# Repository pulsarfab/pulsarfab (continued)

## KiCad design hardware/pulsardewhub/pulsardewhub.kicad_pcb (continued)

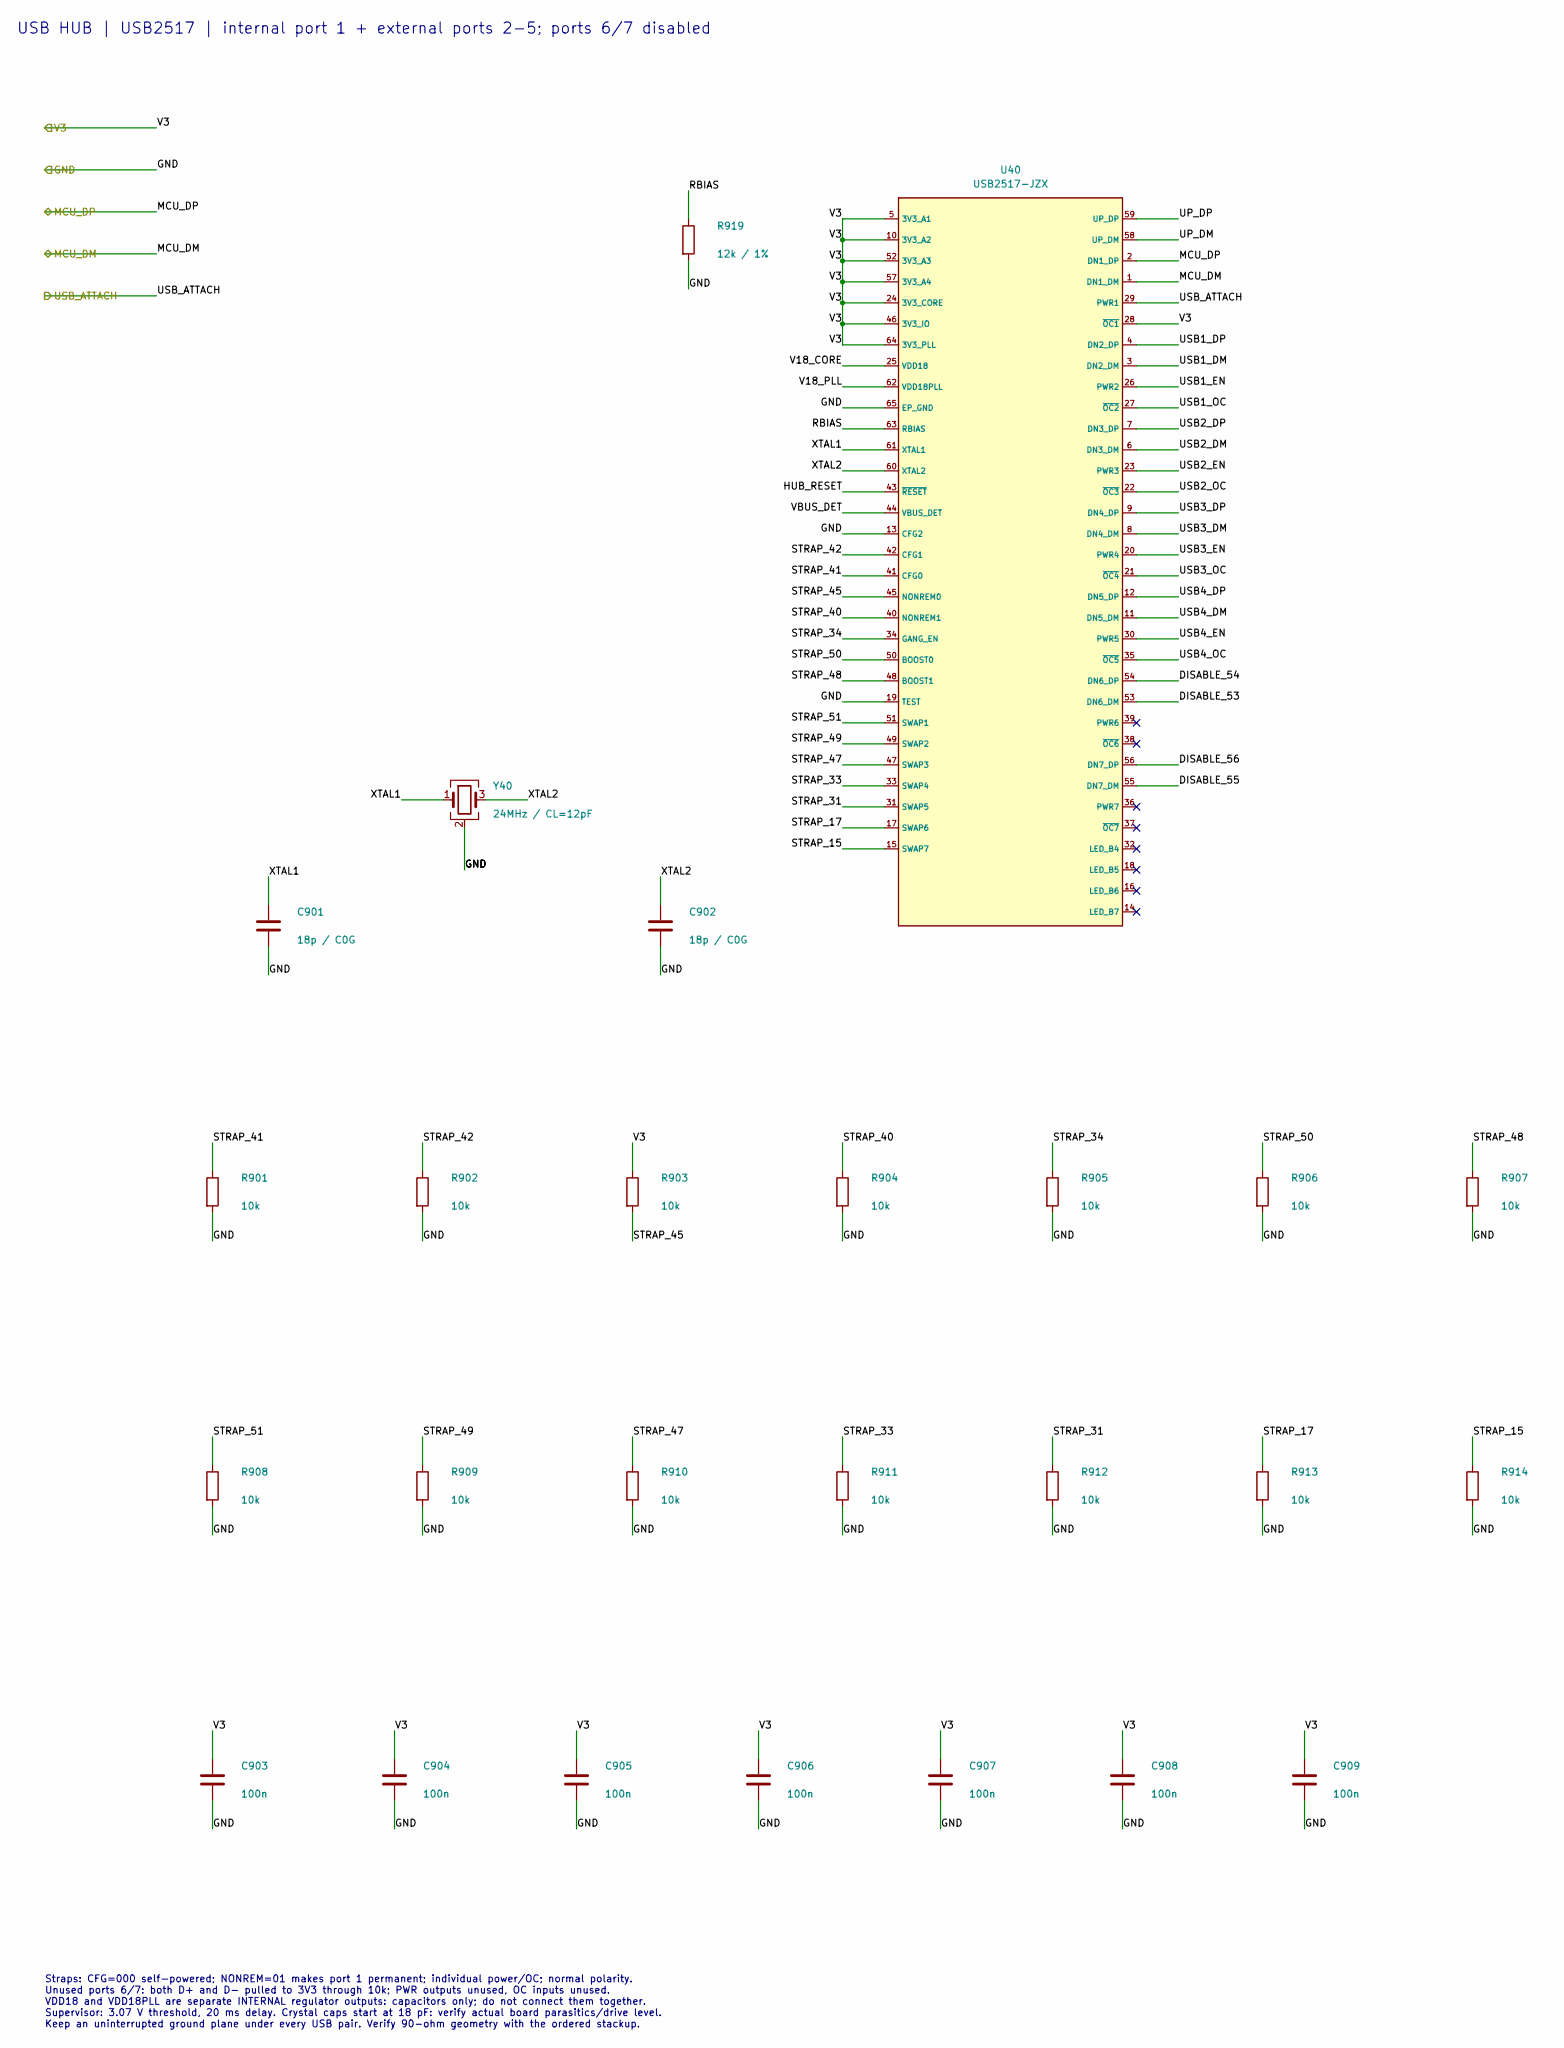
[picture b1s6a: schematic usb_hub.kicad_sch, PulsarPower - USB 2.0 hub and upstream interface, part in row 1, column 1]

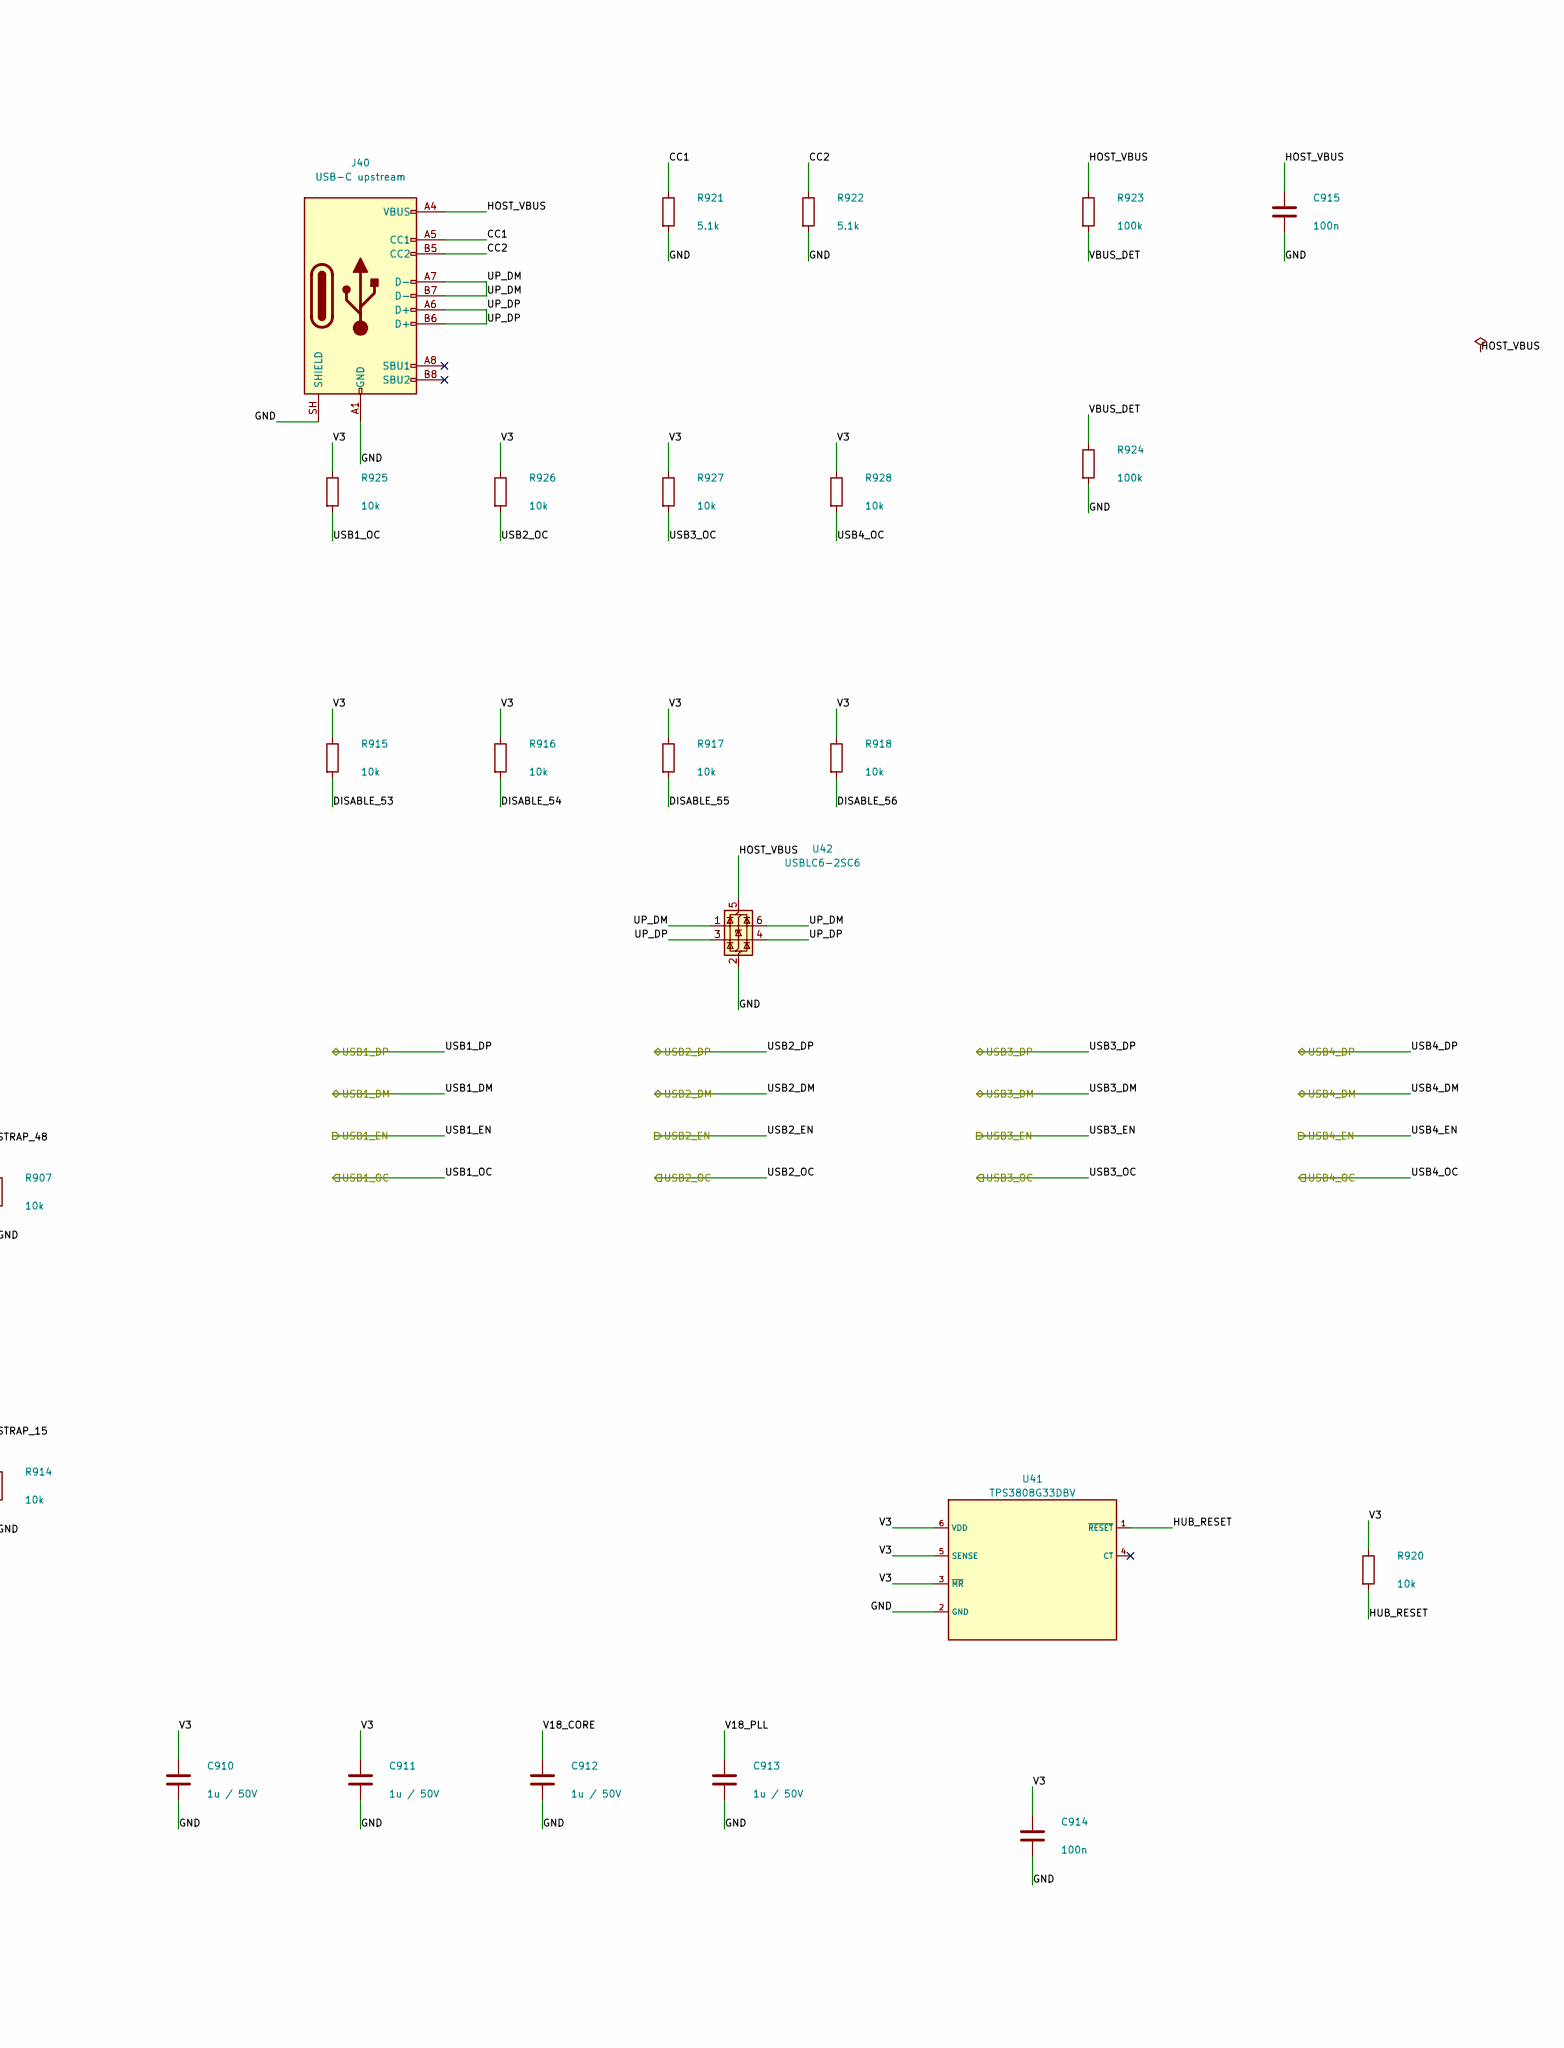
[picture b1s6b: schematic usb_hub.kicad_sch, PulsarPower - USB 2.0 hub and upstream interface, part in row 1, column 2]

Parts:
C901, C902: 18p / C0G; C_0603_1608Metric; MPN CGA3E2C0G1H180JT0Y0N; LCSC C342890
C903, C904, C905, C906, C907, C908, C909, C914, C915: 100n; C_0603_1608Metric; MPN CC0603KRX7R9BB104; LCSC C14663
C910, C911, C912, C913: 1u / 50V; C_0603_1608Metric; MPN CL10A105KB8NNNC; LCSC C15849
J40: USB-C upstream; USB_C_HRO_TYPE-C-31-M-12; MPN TYPE-C-31-M-12; LCSC C165948
R901, R902, R903, R904, R905, R906, R907, R908, R909, R910, R911, R912, R913, R914, R915, R916, R917, R918, R920, R925, R926, R927, R928: 10k; R_0603_1608Metric; MPN 0603WAF1002T5E; LCSC C25804
R919: 12k / 1%; R_0603_1608Metric; MPN 0603WAF1202T5E; LCSC C22790
R921, R922: 5.1k; R_0603_1608Metric; MPN 0603WAF5101T5E; LCSC C23186
R923, R924: 100k; R_0603_1608Metric; MPN 0603WAF1003T5E; LCSC C25803
U40: USB2517-JZX; QFN-64-1EP_9x9mm_P0.5mm_EP4.7x4.7mm; MPN USB2517-JZX; LCSC C1521556
U41: TPS3808G33DBV; SOT-23-6; MPN TPS3808G33DBVR; LCSC C43698
U42: USBLC6-2SC6; SOT-23-6; MPN USBLC6-2SC6; LCSC C7519
Y40: 24MHz / CL=12pF; Crystal_SMD_3225-4Pin_3.2x2.5mm; MPN 3225 24M 12PF 10PPM; LCSC C5181479

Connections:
/GND: C901.2, C902.2, C903.2, C904.2, C905.2, C906.2, C907.2, C908.2, C909.2, C910.2, C911.2, C912.2, C913.2, C914.2, C915.2, J40.A1 (GND), J40.A12 (GND), J40.B1 (GND), J40.B12 (GND), J40.SH (SHIELD), R901.2, R902.2, R904.2, R905.2, R906.2, R907.2, R908.2, R909.2, R910.2, R911.2, R912.2, R913.2, R914.2, R919.2, R921.2, R922.2, R924.2, U40.13 (CFG2), U40.19 (TEST), U40.65 (EP_GND), U41.2 (GND), U42.2 (GND), Y40.2 (G), Y40.4 (G); also elsewhere on the board
/MCU_DM: U40.1 (DN1_DM); also elsewhere on the board
/MCU_DP: U40.2 (DN1_DP); also elsewhere on the board
/USB1_DM: U40.3 (DN2_DM); also elsewhere on the board
/USB1_DP: U40.4 (DN2_DP); also elsewhere on the board
/USB1_EN: U40.26 (PWR2); also elsewhere on the board
/USB1_OC: R925.2, U40.27 (~OC2); also elsewhere on the board
/USB2_DM: U40.6 (DN3_DM); also elsewhere on the board
/USB2_DP: U40.7 (DN3_DP); also elsewhere on the board
/USB2_EN: U40.23 (PWR3); also elsewhere on the board
/USB2_OC: R926.2, U40.22 (~OC3); also elsewhere on the board
/USB3_DM: U40.8 (DN4_DM); also elsewhere on the board
/USB3_DP: U40.9 (DN4_DP); also elsewhere on the board
/USB3_EN: U40.20 (PWR4); also elsewhere on the board
/USB3_OC: R927.2, U40.21 (~OC4); also elsewhere on the board
/USB4_DM: U40.11 (DN5_DM); also elsewhere on the board
/USB4_DP: U40.12 (DN5_DP); also elsewhere on the board
/USB4_EN: U40.30 (PWR5); also elsewhere on the board
/USB4_OC: R928.2, U40.35 (~OC5); also elsewhere on the board
/USB hub/CC1: J40.A5 (CC1), R921.1
/USB hub/CC2: J40.B5 (CC2), R922.1
/USB hub/DISABLE_53: R915.2, U40.53 (DN6_DM)
/USB hub/DISABLE_54: R916.2, U40.54 (DN6_DP)
/USB hub/DISABLE_55: R917.2, U40.55 (DN7_DM)
/USB hub/DISABLE_56: R918.2, U40.56 (DN7_DP)
/USB hub/HOST_VBUS: C915.1, J40.A4 (VBUS), J40.A9 (VBUS), J40.B4 (VBUS), J40.B9 (VBUS), R923.1, U42.5 (VBUS)
/USB hub/HUB_RESET: R920.2, U40.43 (~RESET), U41.1 (~RESET)
/USB hub/RBIAS: R919.1, U40.63 (RBIAS)
/USB hub/STRAP_15: R914.1, U40.15 (SWAP7)
/USB hub/STRAP_17: R913.1, U40.17 (SWAP6)
/USB hub/STRAP_31: R912.1, U40.31 (SWAP5)
/USB hub/STRAP_33: R911.1, U40.33 (SWAP4)
/USB hub/STRAP_34: R905.1, U40.34 (GANG_EN)
/USB hub/STRAP_40: R904.1, U40.40 (NONREM1)
/USB hub/STRAP_41: R901.1, U40.41 (CFG0)
/USB hub/STRAP_42: R902.1, U40.42 (CFG1)
/USB hub/STRAP_45: R903.2, U40.45 (NONREM0)
/USB hub/STRAP_47: R910.1, U40.47 (SWAP3)
/USB hub/STRAP_48: R907.1, U40.48 (BOOST1)
/USB hub/STRAP_49: R909.1, U40.49 (SWAP2)
/USB hub/STRAP_50: R906.1, U40.50 (BOOST0)
/USB hub/STRAP_51: R908.1, U40.51 (SWAP1)
/USB hub/UP_DM: J40.A7 (D-), J40.B7 (D-), U40.58 (UP_DM), U42.1 (I/O1), U42.6 (I/O1)
/USB hub/UP_DP: J40.A6 (D+), J40.B6 (D+), U40.59 (UP_DP), U42.3 (I/O2), U42.4 (I/O2)
/USB hub/V18_CORE: C912.1, U40.25 (VDD18)
/USB hub/V18_PLL: C913.1, U40.62 (VDD18PLL)
/USB hub/VBUS_DET: R923.2, R924.1, U40.44 (VBUS_DET)
/USB hub/XTAL1: C901.1, U40.61 (XTAL1), Y40.1
/USB hub/XTAL2: C902.1, U40.60 (XTAL2), Y40.3
/USB_ATTACH: U40.29 (PWR1); also elsewhere on the board
/V3: C903.1, C904.1, C905.1, C906.1, C907.1, C908.1, C909.1, C910.1, C911.1, C914.1, R903.1, R915.1, R916.1, R917.1, R918.1, R920.1, R925.1, R926.1, R927.1, R928.1, U40.5 (3V3_A1), U40.10 (3V3_A2), U40.24 (3V3_CORE), U40.28 (~OC1), U40.46 (3V3_IO), U40.52 (3V3_A3), U40.57 (3V3_A4), U40.64 (3V3_PLL), U41.3 (~MR), U41.5 (SENSE), U41.6 (VDD); also elsewhere on the board

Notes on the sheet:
USB HUB | USB2517 | internal port 1 + external ports 2-5; ports 6/7 disabled
Straps: CFG=000 self-powered; NONREM=01 makes port 1 permanent; individual power/OC; normal polarity. Unused ports 6/7: both D+ and D- pulled to 3V3 through 10k; PWR outputs unused, OC inputs unused. VDD18 and VDD18PLL are separate INTERNAL regulator outputs: capacitors only; do not connect them to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

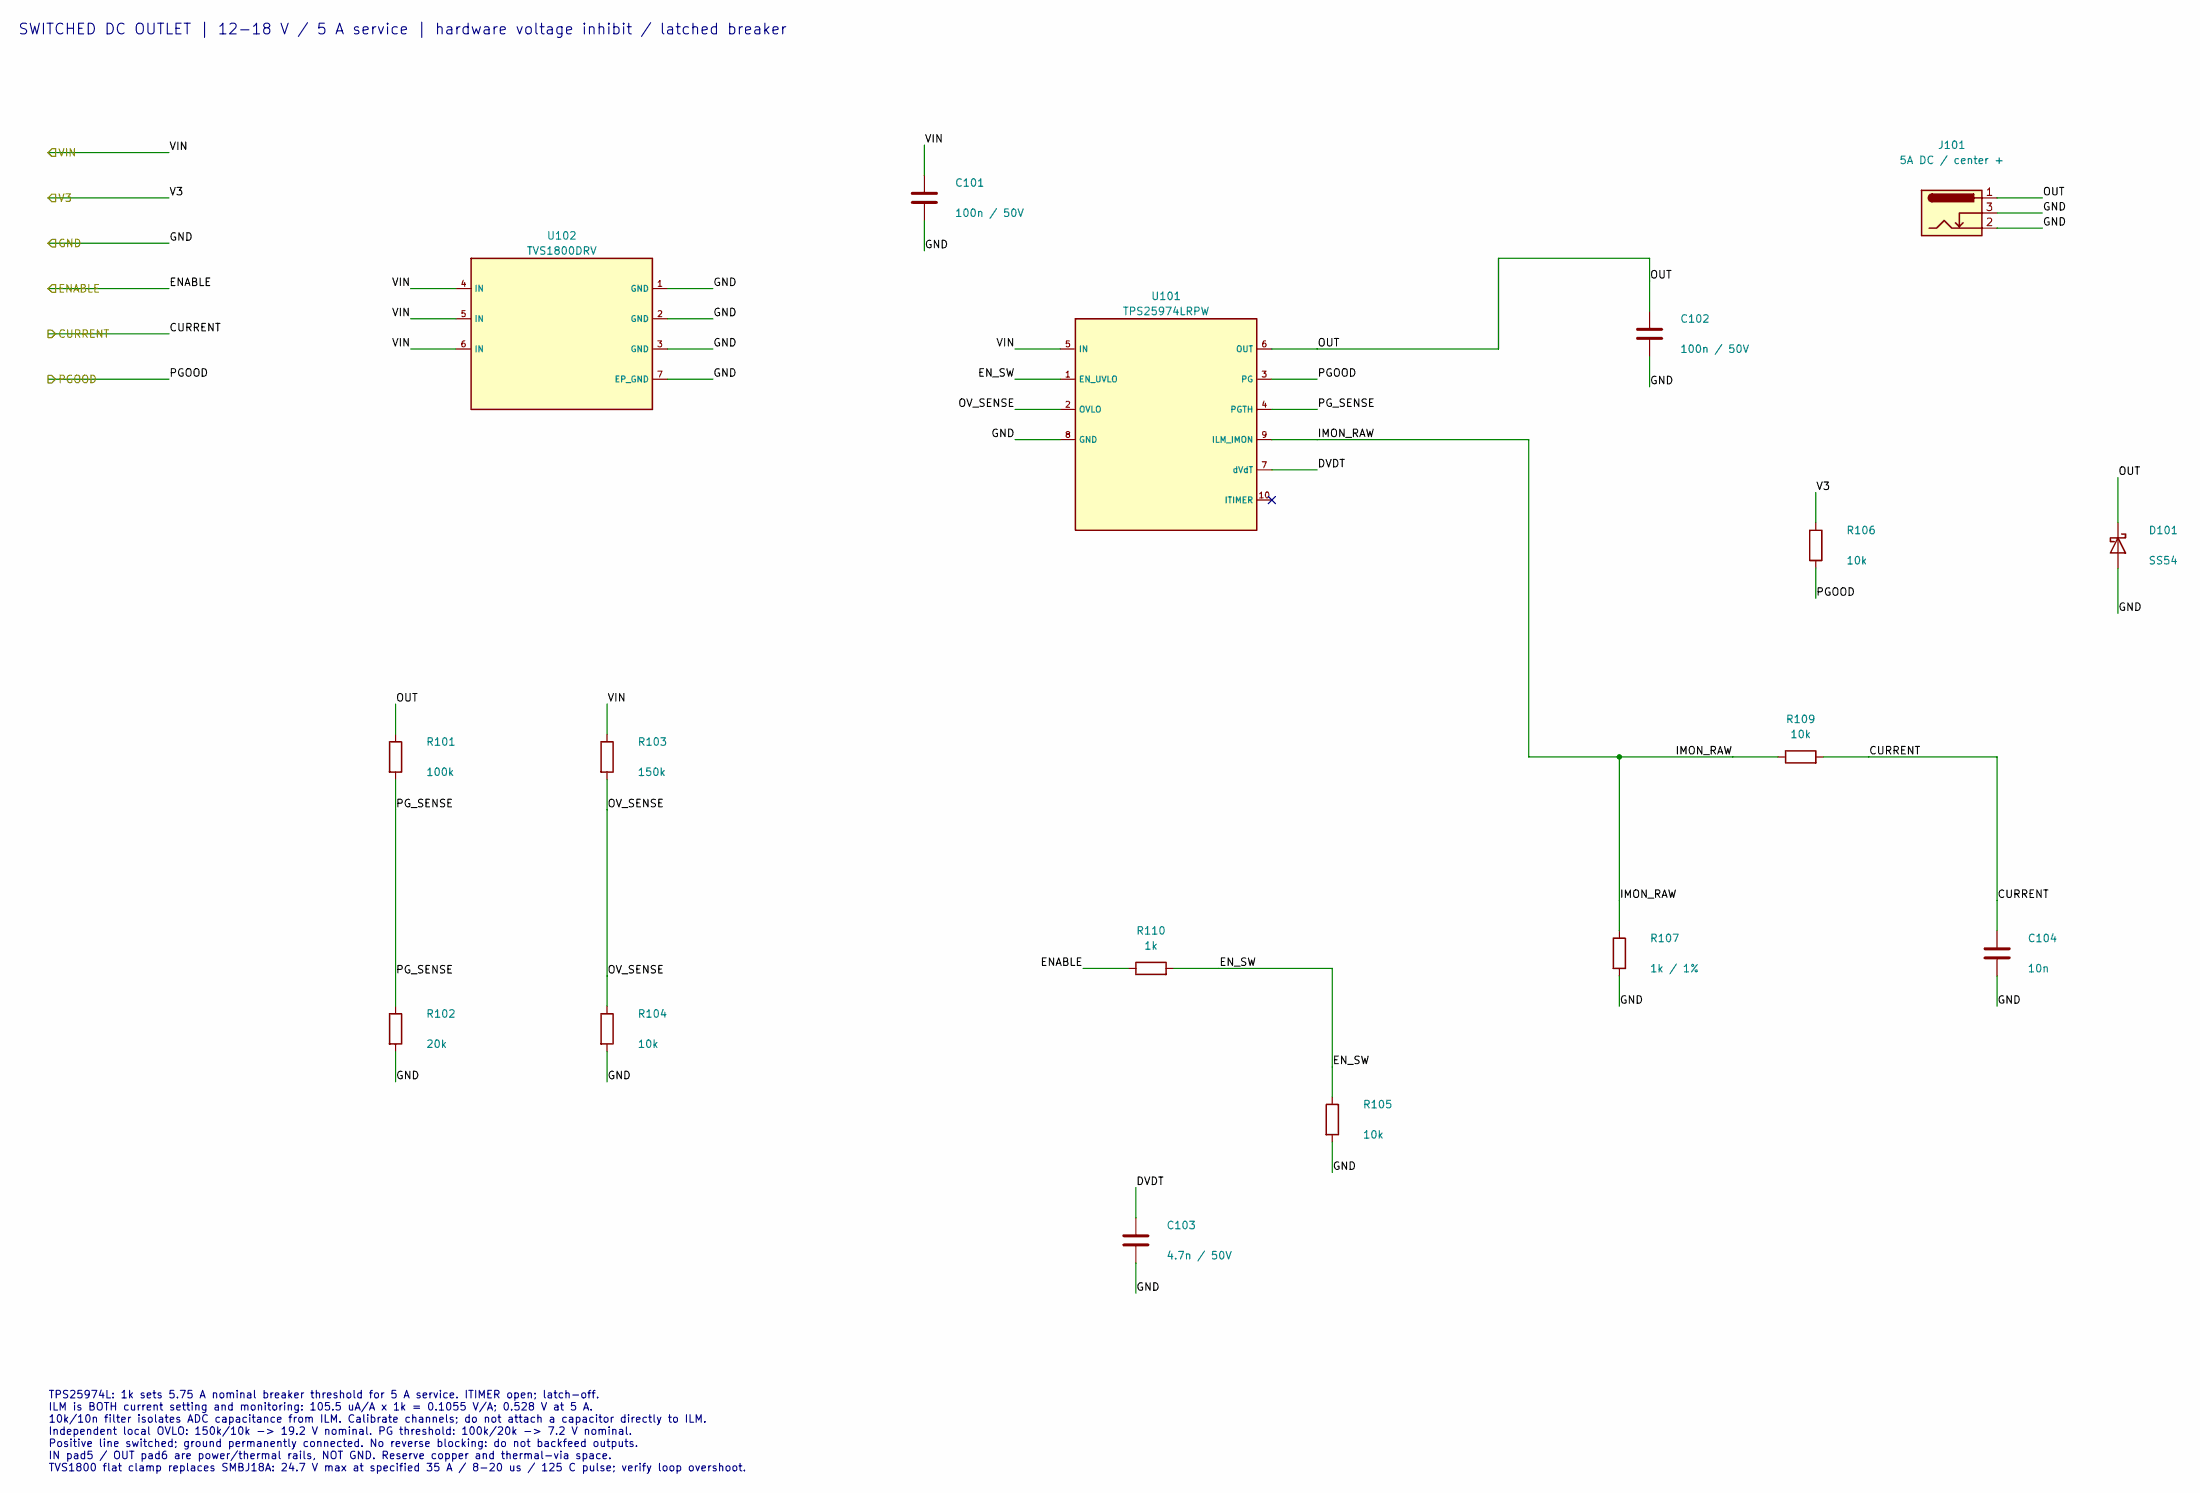
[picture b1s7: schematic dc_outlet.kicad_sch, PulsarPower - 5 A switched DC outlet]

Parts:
C101, C102: 100n / 50V; C_0603_1608Metric; MPN CC0603KRX7R9BB104; LCSC C14663
C103: 4.7n / 50V; C_0603_1608Metric; MPN CL10B472KB8NNNC; LCSC C1621
C104: 10n; C_0603_1608Metric; MPN CL10B103KB8NNNC; LCSC C1589
D101: SS54; D_SMA; MPN SS54; LCSC C22452
J101: 5A DC / center +; BarrelJack_XKB_DC-005K-5A_Edge; MPN DC-005K-5A-2.0; LCSC C2880546
R101: 100k; R_0603_1608Metric; MPN 0603WAF1003T5E; LCSC C25803
R102: 20k; R_0603_1608Metric; MPN 0603WAF2002T5E; LCSC C4184
R103: 150k; R_0603_1608Metric; MPN 0603WAF1503T5E; LCSC C22807
R104, R105, R106, R109: 10k; R_0603_1608Metric; MPN 0603WAF1002T5E; LCSC C25804
R107: 1k / 1%; R_0603_1608Metric; MPN 0603WAF1001T5E; LCSC C21190
R110: 1k; R_0603_1608Metric; MPN 0603WAF1001T5E; LCSC C21190
U101: TPS25974LRPW; TI_RPW0010A_VQFN10_2x2mm; MPN TPS25974LRPWR; LCSC C3662931
U102: TVS1800DRV; WSON-6-1EP_2x2mm_P0.65mm_EP1x1.6mm; MPN TVS1800DRVR; LCSC C2649846

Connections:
/DC outlet 1/DVDT: C103.1, U101.7 (dVdT)
/DC outlet 1/EN_SW: R105.1, R110.2, U101.1 (EN_UVLO)
/DC outlet 1/IMON_RAW: R107.1, R109.1, U101.9 (ILM_IMON)
/DC outlet 1/OUT: C102.1, D101.1 (K), J101.1, R101.1, U101.6 (OUT)
/DC outlet 1/OV_SENSE: R103.2, R104.1, U101.2 (OVLO)
/DC outlet 1/PG_SENSE: R101.2, R102.1, U101.4 (PGTH)
/DC_PG1: R106.2, U101.3 (PG); also elsewhere on the board
/DC_SAFE1: R110.1; also elsewhere on the board
/GND: C101.2, C102.2, C103.2, C104.2, D101.2 (A), J101.2, J101.3, R102.2, R104.2, R105.2, R107.2, U101.8 (GND), U102.1 (GND), U102.2 (GND), U102.3 (GND), U102.7 (EP_GND); also elsewhere on the board
/IMON1: C104.1, R109.2; also elsewhere on the board
/V3: R106.1; also elsewhere on the board
/VIN: C101.1, R103.1, U101.5 (IN), U102.4 (IN), U102.5 (IN), U102.6 (IN); also elsewhere on the board

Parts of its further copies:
C201, C202, C301, C302, C401, C402: 100n / 50V; C_0603_1608Metric; MPN CC0603KRX7R9BB104; LCSC C14663
C203, C303, C403: 4.7n / 50V; C_0603_1608Metric; MPN CL10B472KB8NNNC; LCSC C1621
C204, C304, C404: 10n; C_0603_1608Metric; MPN CL10B103KB8NNNC; LCSC C1589
D201, D301, D401: SS54; D_SMA; MPN SS54; LCSC C22452
J201, J301, J401: 5A DC / center +; BarrelJack_XKB_DC-005K-5A_Edge; MPN DC-005K-5A-2.0; LCSC C2880546
R201, R301, R401: 100k; R_0603_1608Metric; MPN 0603WAF1003T5E; LCSC C25803
R202, R302, R402: 20k; R_0603_1608Metric; MPN 0603WAF2002T5E; LCSC C4184
R203, R303, R403: 150k; R_0603_1608Metric; MPN 0603WAF1503T5E; LCSC C22807
R204, R205, R206, R209, R304, R305, R306, R309, R404, R405, R406, R409: 10k; R_0603_1608Metric; MPN 0603WAF1002T5E; LCSC C25804
R207, R307, R407: 1k / 1%; R_0603_1608Metric; MPN 0603WAF1001T5E; LCSC C21190
R210, R310, R410: 1k; R_0603_1608Metric; MPN 0603WAF1001T5E; LCSC C21190
U201, U301, U401: TPS25974LRPW; TI_RPW0010A_VQFN10_2x2mm; MPN TPS25974LRPWR; LCSC C3662931
U202, U302, U402: TVS1800DRV; WSON-6-1EP_2x2mm_P0.65mm_EP1x1.6mm; MPN TVS1800DRVR; LCSC C2649846

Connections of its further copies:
/DC outlet 2/DVDT: C203.1, U201.7 (dVdT)
/DC outlet 2/EN_SW: R205.1, R210.2, U201.1 (EN_UVLO)
/DC outlet 2/IMON_RAW: R207.1, R209.1, U201.9 (ILM_IMON)
/DC outlet 2/OUT: C202.1, D201.1 (K), J201.1, R201.1, U201.6 (OUT)
/DC outlet 2/OV_SENSE: R203.2, R204.1, U201.2 (OVLO)
/DC outlet 2/PG_SENSE: R201.2, R202.1, U201.4 (PGTH)
/DC outlet 3/DVDT: C303.1, U301.7 (dVdT)
/DC outlet 3/EN_SW: R305.1, R310.2, U301.1 (EN_UVLO)
/DC outlet 3/IMON_RAW: R307.1, R309.1, U301.9 (ILM_IMON)
/DC outlet 3/OUT: C302.1, D301.1 (K), J301.1, R301.1, U301.6 (OUT)
/DC outlet 3/OV_SENSE: R303.2, R304.1, U301.2 (OVLO)
/DC outlet 3/PG_SENSE: R301.2, R302.1, U301.4 (PGTH)
/DC outlet 4/DVDT: C403.1, U401.7 (dVdT)
/DC outlet 4/EN_SW: R405.1, R410.2, U401.1 (EN_UVLO)
/DC outlet 4/IMON_RAW: R407.1, R409.1, U401.9 (ILM_IMON)
/DC outlet 4/OUT: C402.1, D401.1 (K), J401.1, R401.1, U401.6 (OUT)
/DC outlet 4/OV_SENSE: R403.2, R404.1, U401.2 (OVLO)
/DC outlet 4/PG_SENSE: R401.2, R402.1, U401.4 (PGTH)
/DC_PG2: R206.2, U201.3 (PG); also elsewhere on the board
/DC_PG3: R306.2, U301.3 (PG); also elsewhere on the board
/DC_PG4: R406.2, U401.3 (PG); also elsewhere on the board
/DC_SAFE2: R210.1; also elsewhere on the board
/DC_SAFE3: R310.1; also elsewhere on the board
/DC_SAFE4: R410.1; also elsewhere on the board
/GND: C201.2, C202.2, C203.2, C204.2, C301.2, C302.2, C303.2, C304.2, C401.2, C402.2, C403.2, C404.2, D201.2 (A), D301.2 (A), D401.2 (A), J201.2, J201.3, J301.2, J301.3, J401.2, J401.3, R202.2, R204.2, R205.2, R207.2, R302.2, R304.2, R305.2, R307.2, R402.2, R404.2, R405.2, R407.2, U201.8 (GND), U202.1 (GND), U202.2 (GND), U202.3 (GND), U202.7 (EP_GND), U301.8 (GND), U302.1 (GND), U302.2 (GND), U302.3 (GND), U302.7 (EP_GND), U401.8 (GND), U402.1 (GND), U402.2 (GND), U402.3 (GND), U402.7 (EP_GND); also elsewhere on the board
/IMON2: C204.1, R209.2; also elsewhere on the board
/IMON3: C304.1, R309.2; also elsewhere on the board
/IMON4: C404.1, R409.2; also elsewhere on the board
/V3: R206.1, R306.1, R406.1; also elsewhere on the board
/VIN: C201.1, C301.1, C401.1, R203.1, R303.1, R403.1, U201.5 (IN), U202.4 (IN), U202.5 (IN), U202.6 (IN), U301.5 (IN), U302.4 (IN), U302.5 (IN), U302.6 (IN), U401.5 (IN), U402.4 (IN), U402.5 (IN), U402.6 (IN); also elsewhere on the board

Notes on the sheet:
SWITCHED DC OUTLET | 12-18 V / 5 A service | hardware voltage inhibit / latched breaker
TPS25974L: 1k sets 5.75 A nominal breaker threshold for 5 A service. ITIMER open; latch-off. ILM is BOTH current setting and monitoring: 105.5 uA/A x 1k = 0.1055 V/A; 0.528 V at 5 A. 10k/10n filter isolates ADC capacitance from ILM. Calibrate channels; do not attach a capacitor directly to ILM. Ind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

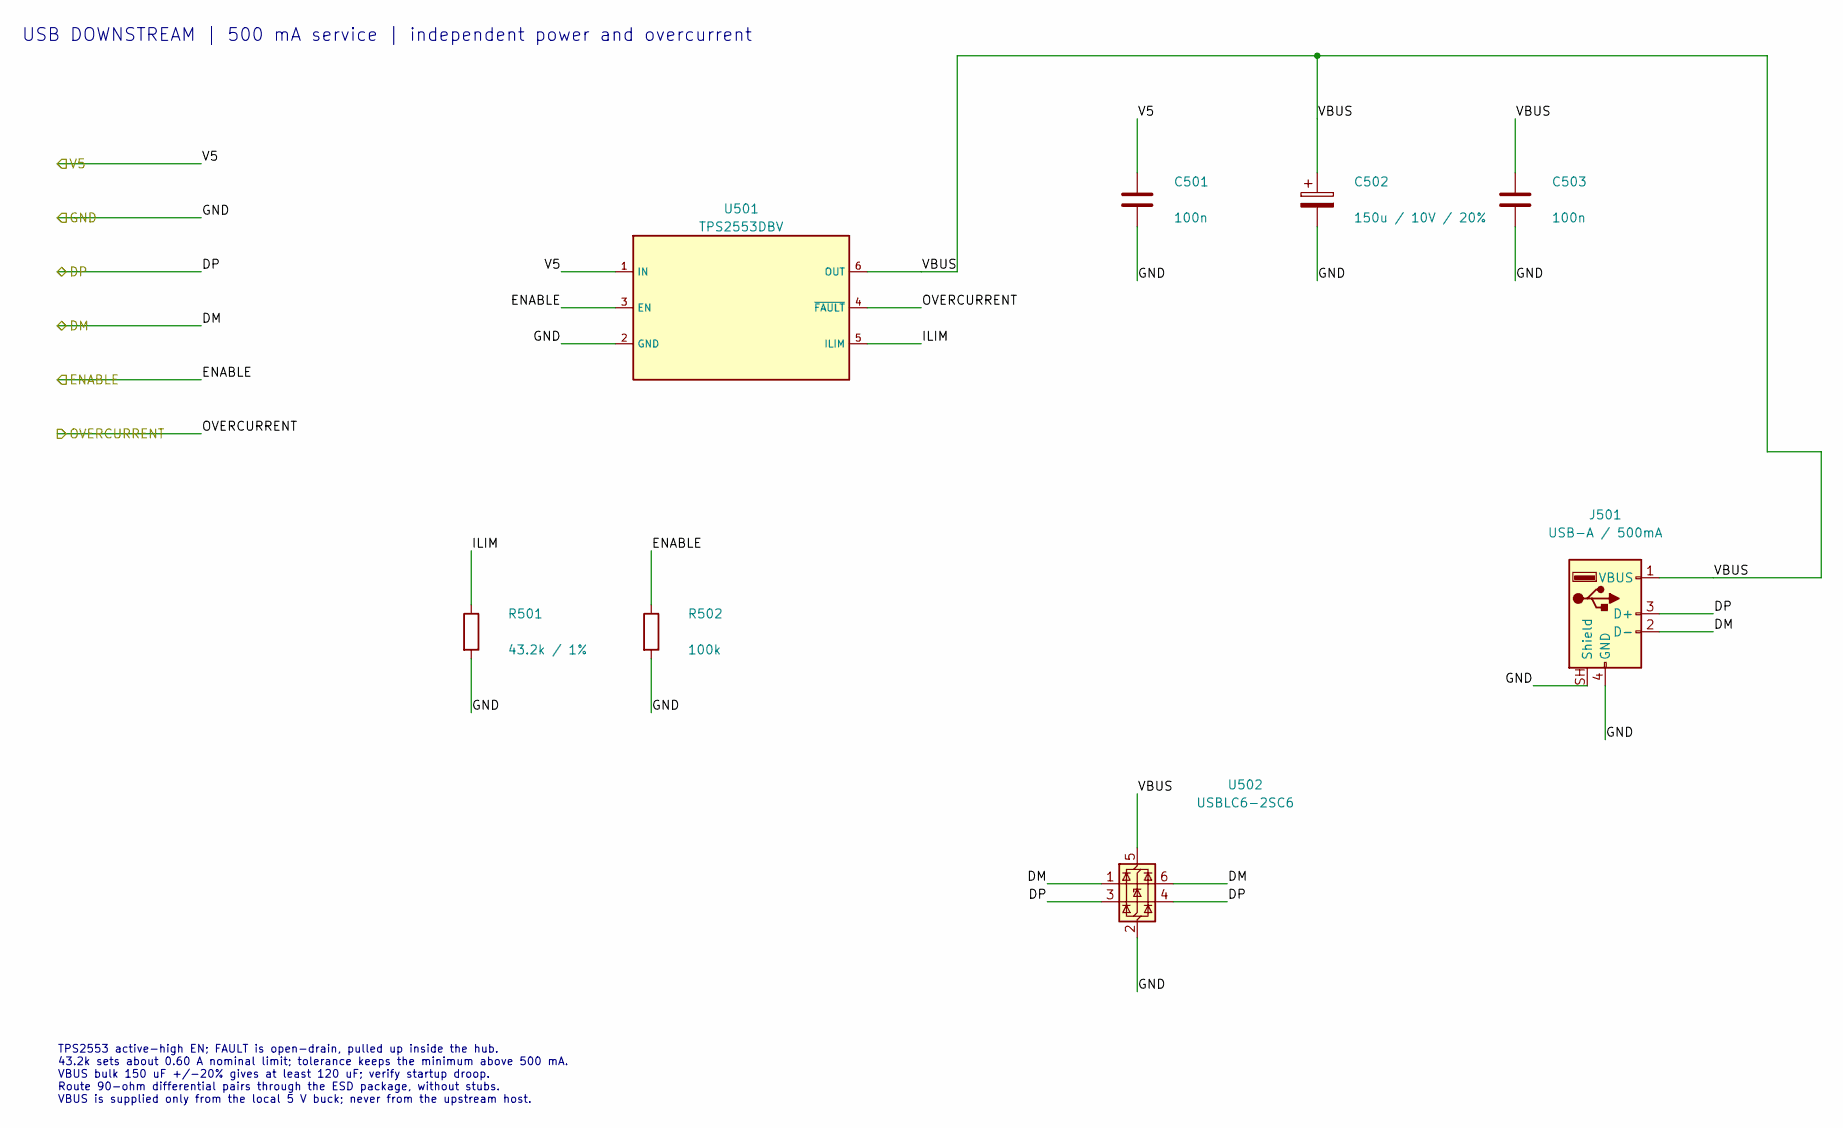
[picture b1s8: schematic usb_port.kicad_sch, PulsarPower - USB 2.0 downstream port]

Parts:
C501, C503: 100n; C_0603_1608Metric; MPN CC0603KRX7R9BB104; LCSC C14663
C502: 150u / 10V / 20%; CP_RVT_D6.3mm_L5.4mm; MPN RVT1A151M0605 150UF 10V; LCSC C970688
J501: USB-A / 500mA; USB_A_SHOUHAN_AF90ZJWG_THT; MPN AF 90 ZJWG; LCSC C456019
R501: 43.2k / 1%; R_0603_1608Metric; MPN 0603WAF4322T5E; LCSC C23053
R502: 100k; R_0603_1608Metric; MPN 0603WAF1003T5E; LCSC C25803
U501: TPS2553DBV; SOT-23-6; MPN TPS2553DBVR; LCSC C55266
U502: USBLC6-2SC6; SOT-23-6; MPN USBLC6-2SC6; LCSC C7519

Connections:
/GND: C501.2, C502.2, C503.2, J501.4 (GND), J501.SH (Shield), R501.2, R502.2, U501.2 (GND), U502.2 (GND); also elsewhere on the board
/USB1_DM: J501.2 (D-), U502.1 (I/O1), U502.6 (I/O1); also elsewhere on the board
/USB1_DP: J501.3 (D+), U502.3 (I/O2), U502.4 (I/O2); also elsewhere on the board
/USB1_EN: R502.1, U501.3 (EN); also elsewhere on the board
/USB1_OC: U501.4 (~FAULT); also elsewhere on the board
/USB port 1/ILIM: R501.1, U501.5 (ILIM)
/USB port 1/VBUS: C502.1, C503.1, J501.1 (VBUS), U501.6 (OUT), U502.5 (VBUS)
/V5: C501.1, U501.1 (IN); also elsewhere on the board

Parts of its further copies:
C601, C603, C701, C703, C801, C803: 100n; C_0603_1608Metric; MPN CC0603KRX7R9BB104; LCSC C14663
C602, C702, C802: 150u / 10V / 20%; CP_RVT_D6.3mm_L5.4mm; MPN RVT1A151M0605 150UF 10V; LCSC C970688
J601, J701, J801: USB-A / 500mA; USB_A_SHOUHAN_AF90ZJWG_THT; MPN AF 90 ZJWG; LCSC C456019
R601, R701, R801: 43.2k / 1%; R_0603_1608Metric; MPN 0603WAF4322T5E; LCSC C23053
R602, R702, R802: 100k; R_0603_1608Metric; MPN 0603WAF1003T5E; LCSC C25803
U601, U701, U801: TPS2553DBV; SOT-23-6; MPN TPS2553DBVR; LCSC C55266
U602, U702, U802: USBLC6-2SC6; SOT-23-6; MPN USBLC6-2SC6; LCSC C7519

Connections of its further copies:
/GND: C601.2, C602.2, C603.2, C701.2, C702.2, C703.2, C801.2, C802.2, C803.2, J601.4 (GND), J601.SH (Shield), J701.4 (GND), J701.SH (Shield), J801.4 (GND), J801.SH (Shield), R601.2, R602.2, R701.2, R702.2, R801.2, R802.2, U601.2 (GND), U602.2 (GND), U701.2 (GND), U702.2 (GND), U801.2 (GND), U802.2 (GND); also elsewhere on the board
/USB2_DM: J601.2 (D-), U602.1 (I/O1), U602.6 (I/O1); also elsewhere on the board
/USB2_DP: J601.3 (D+), U602.3 (I/O2), U602.4 (I/O2); also elsewhere on the board
/USB2_EN: R602.1, U601.3 (EN); also elsewhere on the board
/USB2_OC: U601.4 (~FAULT); also elsewhere on the board
/USB3_DM: J701.2 (D-), U702.1 (I/O1), U702.6 (I/O1); also elsewhere on the board
/USB3_DP: J701.3 (D+), U702.3 (I/O2), U702.4 (I/O2); also elsewhere on the board
/USB3_EN: R702.1, U701.3 (EN); also elsewhere on the board
/USB3_OC: U701.4 (~FAULT); also elsewhere on the board
/USB4_DM: J801.2 (D-), U802.1 (I/O1), U802.6 (I/O1); also elsewhere on the board
/USB4_DP: J801.3 (D+), U802.3 (I/O2), U802.4 (I/O2); also elsewhere on the board
/USB4_EN: R802.1, U801.3 (EN); also elsewhere on the board
/USB4_OC: U801.4 (~FAULT); also elsewhere on the board
/USB port 2/ILIM: R601.1, U601.5 (ILIM)
/USB port 2/VBUS: C602.1, C603.1, J601.1 (VBUS), U601.6 (OUT), U602.5 (VBUS)
/USB port 3/ILIM: R701.1, U701.5 (ILIM)
/USB port 3/VBUS: C702.1, C703.1, J701.1 (VBUS), U701.6 (OUT), U702.5 (VBUS)
/USB port 4/ILIM: R801.1, U801.5 (ILIM)
/USB port 4/VBUS: C802.1, C803.1, J801.1 (VBUS), U801.6 (OUT), U802.5 (VBUS)
/V5: C601.1, C701.1, C801.1, U601.1 (IN), U701.1 (IN), U801.1 (IN); also elsewhere on the board

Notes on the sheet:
USB DOWNSTREAM | 500 mA service | independent power and overcurrent
TPS2553 active-high EN; FAULT is open-drain, pulled up inside the hub. 43.2k sets about 0.60 A nominal limit; tolerance keeps the minimum above 500 mA. VBUS bulk 150 uF +/-20% gives at least 120 uF; verify startup droop. Route 90-ohm differential pairs through the ESD package, without stubs. VBUS i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

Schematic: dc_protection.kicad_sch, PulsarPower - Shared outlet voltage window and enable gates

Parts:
C70, C71: 100n; C_0603_1608Metric; MPN CC0603KRX7R9BB104; LCSC C14663
R70: 220k; R_0603_1608Metric; MPN 0603WAF2203T5E; LCSC C22961
R71, R73, R74, R75, R76, R77, R78: 10k; R_0603_1608Metric; MPN 0603WAF1002T5E; LCSC C25804
R72: 470k; R_0603_1608Metric; MPN 0603WAF4703T5E; LCSC C23178
U70: TPS3700DDC; SOT-23-6; MPN TPS3700DDCR; LCSC C33002
U71: SN74LVC08APW; TSSOP-14_4.4x5mm_P0.65mm; MPN SN74LVC08APWR; LCSC C465737

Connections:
/DC protection/OV_SENSE: R72.2, R73.1, U70.4 (INB-)
/DC protection/UV_SENSE: R70.2, R71.1, U70.3 (INA+)
/DC protection/WINDOW_OK: R74.2, U70.1 (OUTA), U70.6 (OUTB), U71.2 (1B), U71.5 (2B), U71.10 (3B), U71.13 (4B)
/DC_EN1: R75.1, U71.1 (1A); also elsewhere on the board
/DC_EN2: R76.1, U71.4 (2A); also elsewhere on the board
/DC_EN3: R77.1, U71.9 (3A); also elsewhere on the board
/DC_EN4: R78.1, U71.12 (4A); also elsewhere on the board
/DC_SAFE1: U71.3 (1Y); also elsewhere on the board
/DC_SAFE2: U71.6 (2Y); also elsewhere on the board
/DC_SAFE3: U71.8 (3Y); also elsewhere on the board
/DC_SAFE4: U71.11 (4Y); also elsewhere on the board
/GND: C70.2, C71.2, R71.2, R73.2, R75.2, R76.2, R77.2, R78.2, U70.2 (GND), U71.7 (GND); also elsewhere on the board
/V3: C70.1, C71.1, R74.1, U70.5 (VDD), U71.14 (VCC); also elsewhere on the board
/VIN: R70.1, R72.1; also elsewhere on the board

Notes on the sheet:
DC PROTECTION | one hardware voltage window | four independent default-off commands
TPS3700: 9.2 V UV rising / 19.2 V OV rising nominal. Open-drain outputs wired together. 74LVC08: ENi = CMDi AND WINDOW_OK; each command has a 10k pulldown. Each outlet also has an EN pulldown: reset, missing logic supply and disconnected command request OFF. A voltage recovery can re-enable an asse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

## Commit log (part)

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2026-06-27 ci(deps): bump actions/checkout from 6 to 7
    Bumps [actions/checkout](https://github.com/actions/checkout) from 6 to 7.
    - [Release notes](https://github.com/actions/checkout/releases)
    - [Changelog](https://github.com/actions/checkout/blob/main/CHANGELOG.md)
    - [Commits](https://github.com/actions/checkout/compare/v6...v7)
    ---
    updated-dependencies:
2026-06-27 deps(deps): bump firmware/common/STM32CubeG0 from `abbbbed` to `b1d88f9`
    Bumps [firmware/common/STM32CubeG0](https://github.com/STMicroelectronics/STM32CubeG0) from `abbbbed` to `b1d88f9`.
    - [Commits](https://github.com/STMicroelectronics/STM32CubeG0/compare/abbbbed4adffb8715a922ea0b81ae9e3141b3cb3...b1d88f9e17290d5c5328399bb02bb5ef82deb03a)
    ---
    updated-dependencies:
    - dependency-name: firmware/common/STM32CubeG0
    dependency-version: b1d88f9e17290d5c5328399bb02bb5ef82deb03a
